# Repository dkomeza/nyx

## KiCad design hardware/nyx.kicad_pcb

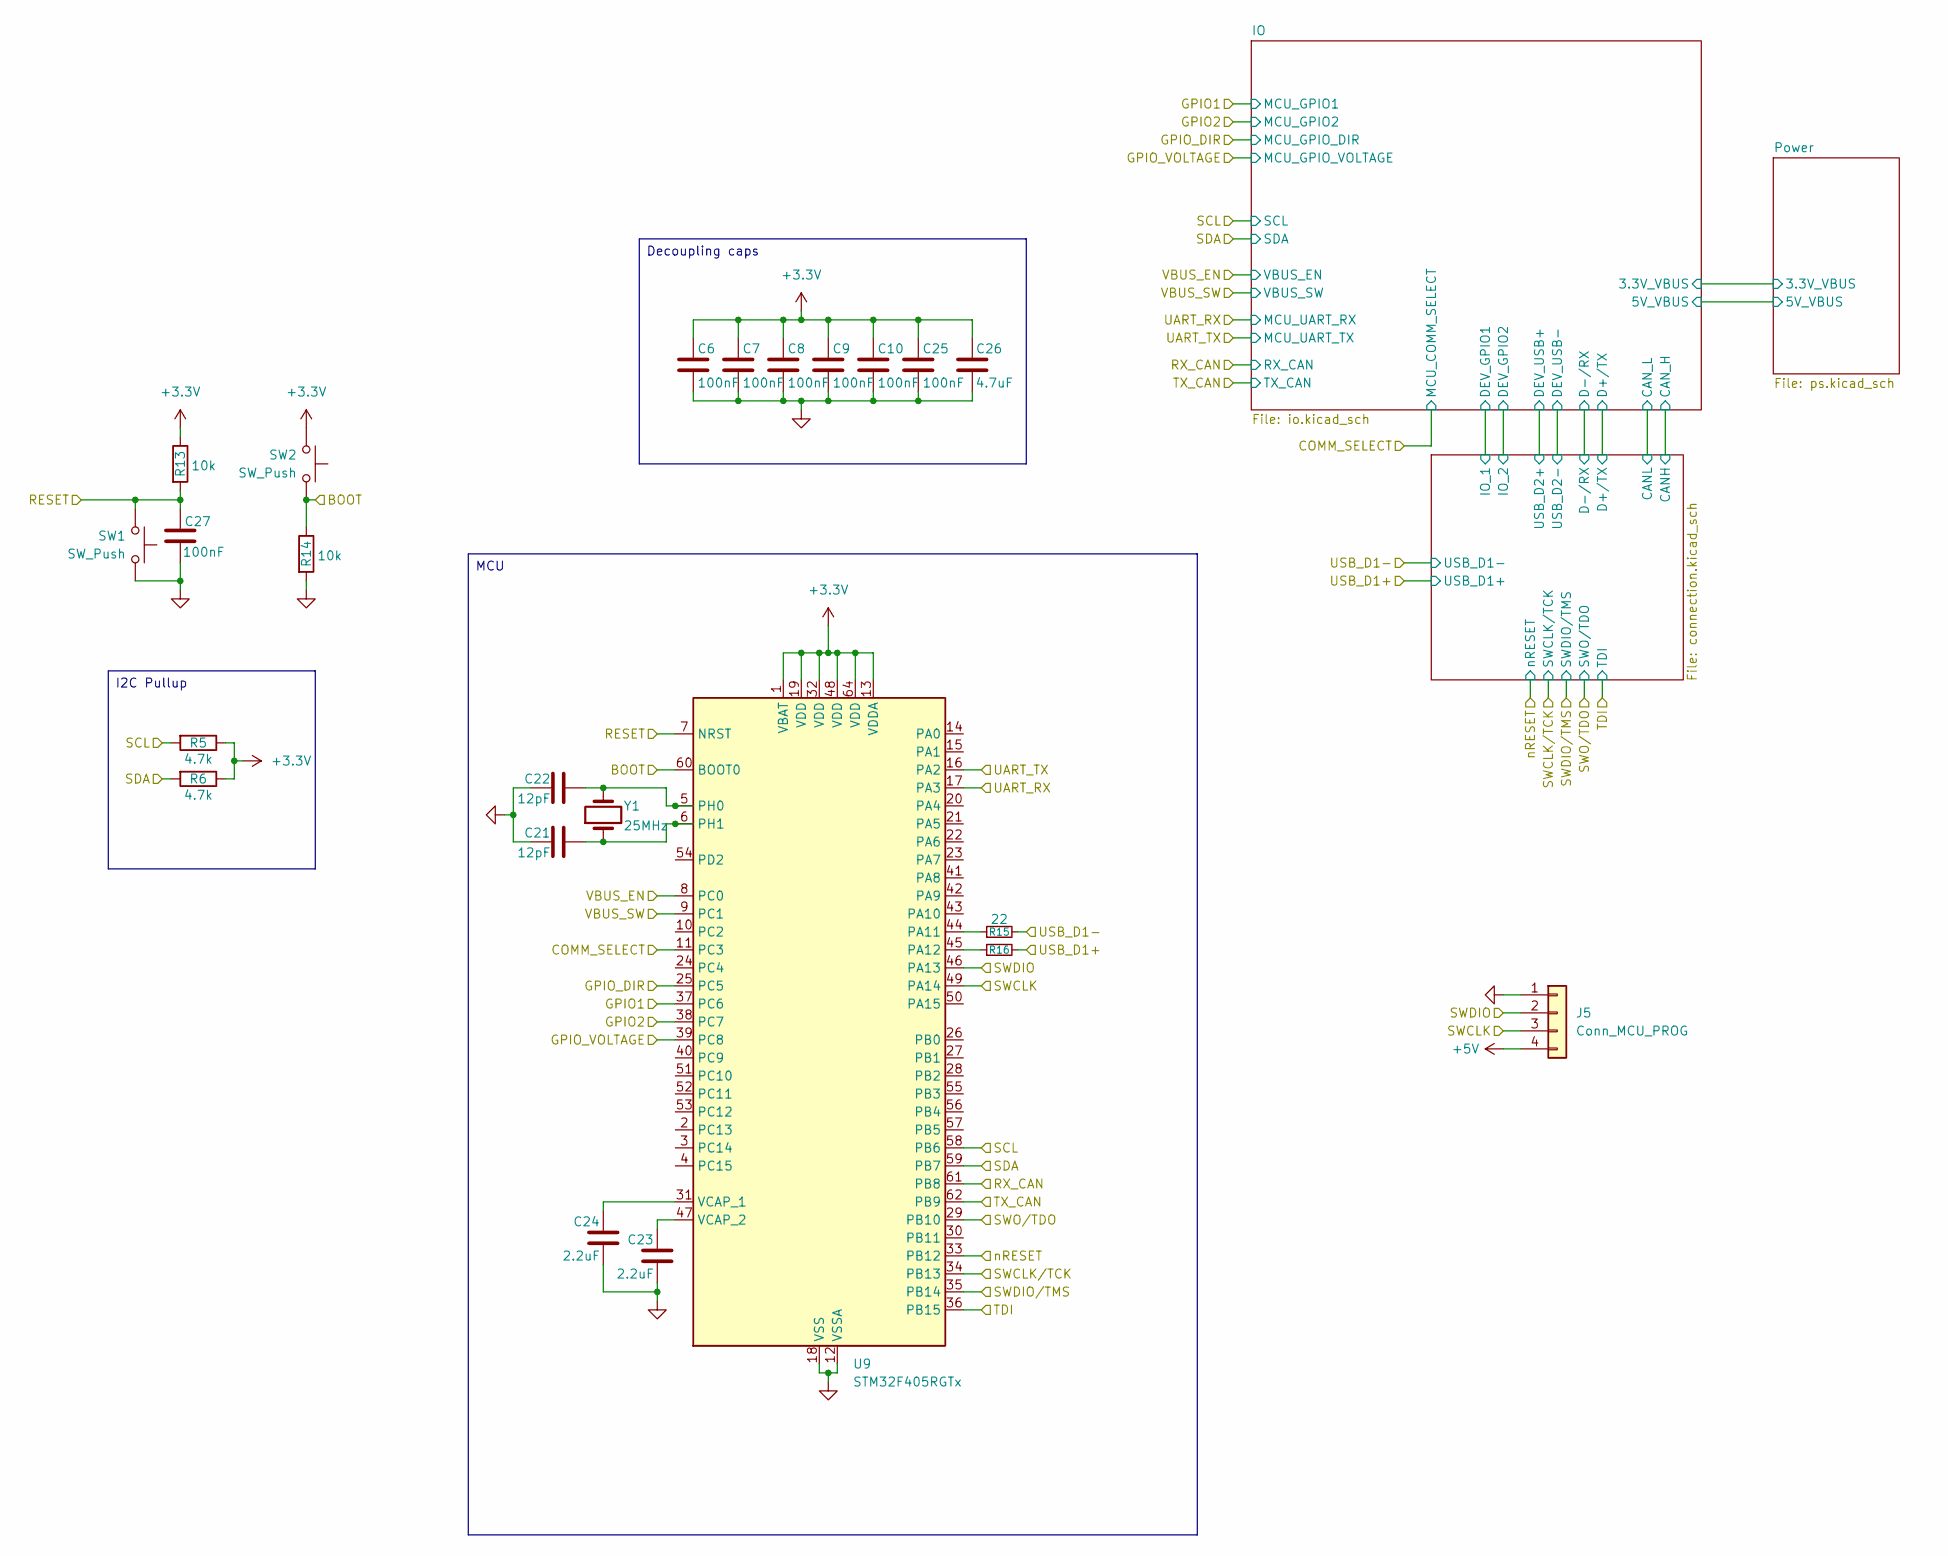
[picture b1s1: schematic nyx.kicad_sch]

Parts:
C6, C7, C8, C9, C10, C25, C27: 100nF; C_0402_1005Metric
C21, C22: 12pF; C_0402_1005Metric
C23, C24: 2.2uF; C_0603_1608Metric
C26: 4.7uF; C_0603_1608Metric
J5: Conn_MCU_PROG; PinHeader_1x04_P2.54mm_Vertical
R5, R6: 4.7k; R_0603_1608Metric
R13, R14: 10k; R_0603_1608Metric
R15, R16: 22; R_0603_1608Metric
SW1, SW2: SW_Push; SW_SPST_B3U-1000P
U9: STM32F405RGTx; LQFP-64_10x10mm_P0.5mm
Y1: 25MHz; Crystal_SMD_2016-4Pin_2.0x1.6mm

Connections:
+3.3V: C6.1, C7.1, C8.1, C9.1, C10.1, C25.1, C26.1, R5.1, R6.1, R13.1, SW2.2, U9.1 (VBAT), U9.13 (VDDA), U9.19 (VDD), U9.32 (VDD), U9.48 (VDD), U9.64 (VDD); also elsewhere on the board
+5V: J5.4; also elsewhere on the board
/BOOT: R14.1, SW2.1, U9.60 (BOOT0)
/COMM_SELECT: U9.11 (PC3); also elsewhere on the board
/GPIO1: U9.37 (PC6); also elsewhere on the board
/GPIO2: U9.38 (PC7); also elsewhere on the board
/GPIO_DIR: U9.25 (PC5); also elsewhere on the board
/GPIO_VOLTAGE: U9.39 (PC8); also elsewhere on the board
/RESET: C27.1, R13.2, SW1.2, U9.7 (NRST)
/RX_CAN: U9.61 (PB8); also elsewhere on the board
/SCL: R5.2, U9.58 (PB6); also elsewhere on the board
/SDA: R6.2, U9.59 (PB7); also elsewhere on the board
/SWCLK: J5.3, U9.49 (PA14)
/SWCLK/TCK: U9.34 (PB13); also elsewhere on the board
/SWDIO: J5.2, U9.46 (PA13)
/SWDIO/TMS: U9.35 (PB14); also elsewhere on the board
/SWO/TDO: U9.29 (PB10); also elsewhere on the board
/TDI: U9.36 (PB15); also elsewhere on the board
/TX_CAN: U9.62 (PB9); also elsewhere on the board
/UART_RX: U9.17 (PA3); also elsewhere on the board
/UART_TX: U9.16 (PA2); also elsewhere on the board
/USB_D1+: R16.2; also elsewhere on the board
/USB_D1-: R15.2; also elsewhere on the board
/VBUS_EN: U9.8 (PC0); also elsewhere on the board
/VBUS_SW: U9.9 (PC1); also elsewhere on the board
/nRESET: U9.33 (PB12); also elsewhere on the board
GND: C6.2, C7.2, C8.2, C9.2, C10.2, C21.1, C22.1, C23.2, C24.2, C25.2, C26.2, C27.2, J5.1, R14.2, SW1.1, U9.12 (VSSA), U9.18 (VSS), U9.63 (VSS); also elsewhere on the board
unnamed: R15.1, U9.44 (PA11)
unnamed: R16.1, U9.45 (PA12)
unnamed: C22.2, U9.5 (PH0), Y1.2
unnamed: C21.2, U9.6 (PH1), Y1.1
unnamed: C24.1, U9.31 (VCAP_1)
unnamed: C23.1, U9.47 (VCAP_2)

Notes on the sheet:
I2C Pullup
MCU
Decoupling caps

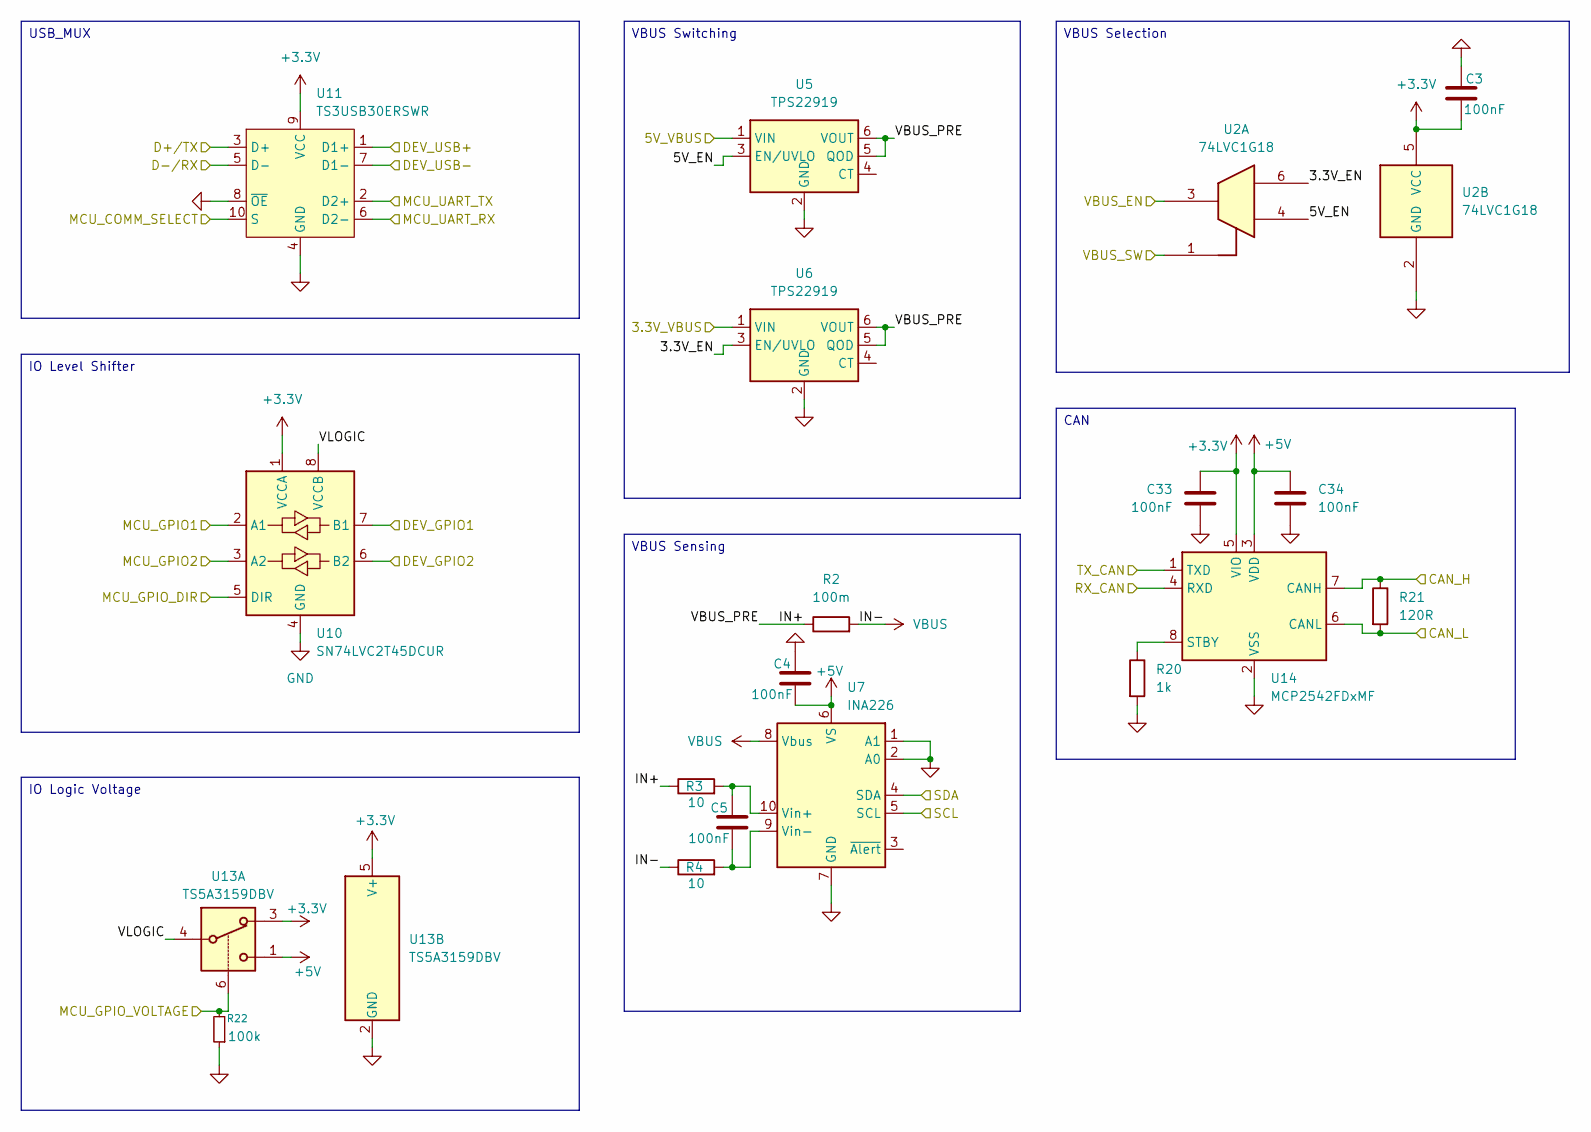
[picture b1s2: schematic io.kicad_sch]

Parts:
C3, C4, C5, C33, C34: 100nF; C_0402_1005Metric
R2: 100m; R_1206_3216Metric
R3, R4: 10; R_0603_1608Metric
R20: 1k; R_0603_1608Metric
R21: 120R; R_0603_1608Metric
R22: 100k; R_0603_1608Metric
U2: 74LVC1G18; SOT-363_SC-70-6
U5, U6: TPS22919; SOT-363_SC-70-6
U7: INA226; VSSOP-10_3x3mm_P0.5mm
U10: SN74LVC2T45DCUR; VSSOP-8_2.3x2mm_P0.5mm
U11: TS3USB30ERSWR; UQFN-10_1.4x1.8mm_P0.4mm
U13: TS5A3159DBV; SOT-23-6
U14: MCP2542FDxMF; DFN-8-1EP_3x3mm_P0.65mm_EP1.55x2.4mm

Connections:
+3.3V: C3.2, C33.1, U2.5 (VCC), U10.1 (VCCA), U11.9 (VCC), U13.3, U13.5 (V+), U14.5 (VIO); also elsewhere on the board
+5V: C4.2, C34.1, U7.6 (VS), U13.1, U14.3 (VDD); also elsewhere on the board
/COMM_SELECT: U11.10 (S); also elsewhere on the board
/Connection/CANH: R21.1, U14.7 (CANH); also elsewhere on the board
/Connection/CANL: R21.2, U14.6 (CANL); also elsewhere on the board
/Connection/D+/TX: U11.3 (D+); also elsewhere on the board
/Connection/D-/RX: U11.5 (D-); also elsewhere on the board
/Connection/IO_1: U10.7 (B1); also elsewhere on the board
/Connection/IO_2: U10.6 (B2); also elsewhere on the board
/Connection/USB_D2+: U11.1 (D1+); also elsewhere on the board
/Connection/USB_D2-: U11.7 (D1-); also elsewhere on the board
/GPIO1: U10.2 (A1); also elsewhere on the board
/GPIO2: U10.3 (A2); also elsewhere on the board
/GPIO_DIR: U10.5 (DIR); also elsewhere on the board
/GPIO_VOLTAGE: R22.2, U13.6; also elsewhere on the board
/IO/3.3V_EN: U2.6, U6.3 (EN/UVLO)
/IO/3.3V_VBUS: U6.1 (VIN); also elsewhere on the board
/IO/5V_EN: U2.4, U5.3 (EN/UVLO)
/IO/5V_VBUS: U5.1 (VIN)
/IO/IN+: R2.1, R3.1, U5.5 (QOD), U5.6 (VOUT), U6.5 (QOD), U6.6 (VOUT)
/IO/VLOGIC: U10.8 (VCCB), U13.4
/RX_CAN: U14.4 (RXD); also elsewhere on the board
/SCL: U7.5 (SCL); also elsewhere on the board
/SDA: U7.4 (SDA); also elsewhere on the board
/TX_CAN: U14.1 (TXD); also elsewhere on the board
/UART_RX: U11.6 (D2-); also elsewhere on the board
/UART_TX: U11.2 (D2+); also elsewhere on the board
/VBUS_EN: U2.3; also elsewhere on the board
/VBUS_SW: U2.1; also elsewhere on the board
GND: C3.1, C4.1, C33.2, C34.2, R20.2, R22.1, U2.2 (GND), U5.2 (GND), U6.2 (GND), U7.1 (A1), U7.2 (A0), U7.7 (GND), U10.4 (GND), U11.4 (GND), U11.8 (~OE), U13.2 (GND), U14.2 (VSS), U14.9 (VSS); also elsewhere on the board
unnamed: C5.1, R3.2, U7.10 (Vin+)
unnamed: C5.2, R4.2, U7.9 (Vin-)
unnamed: R20.1, U14.8 (STBY)
VBUS: R2.2, R4.1, U7.8 (Vbus); also elsewhere on the board

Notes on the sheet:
USB_MUX
IO Level Shifter
VBUS Selection
VBUS Sensing
IO Logic Voltage
VBUS Switching
CAN

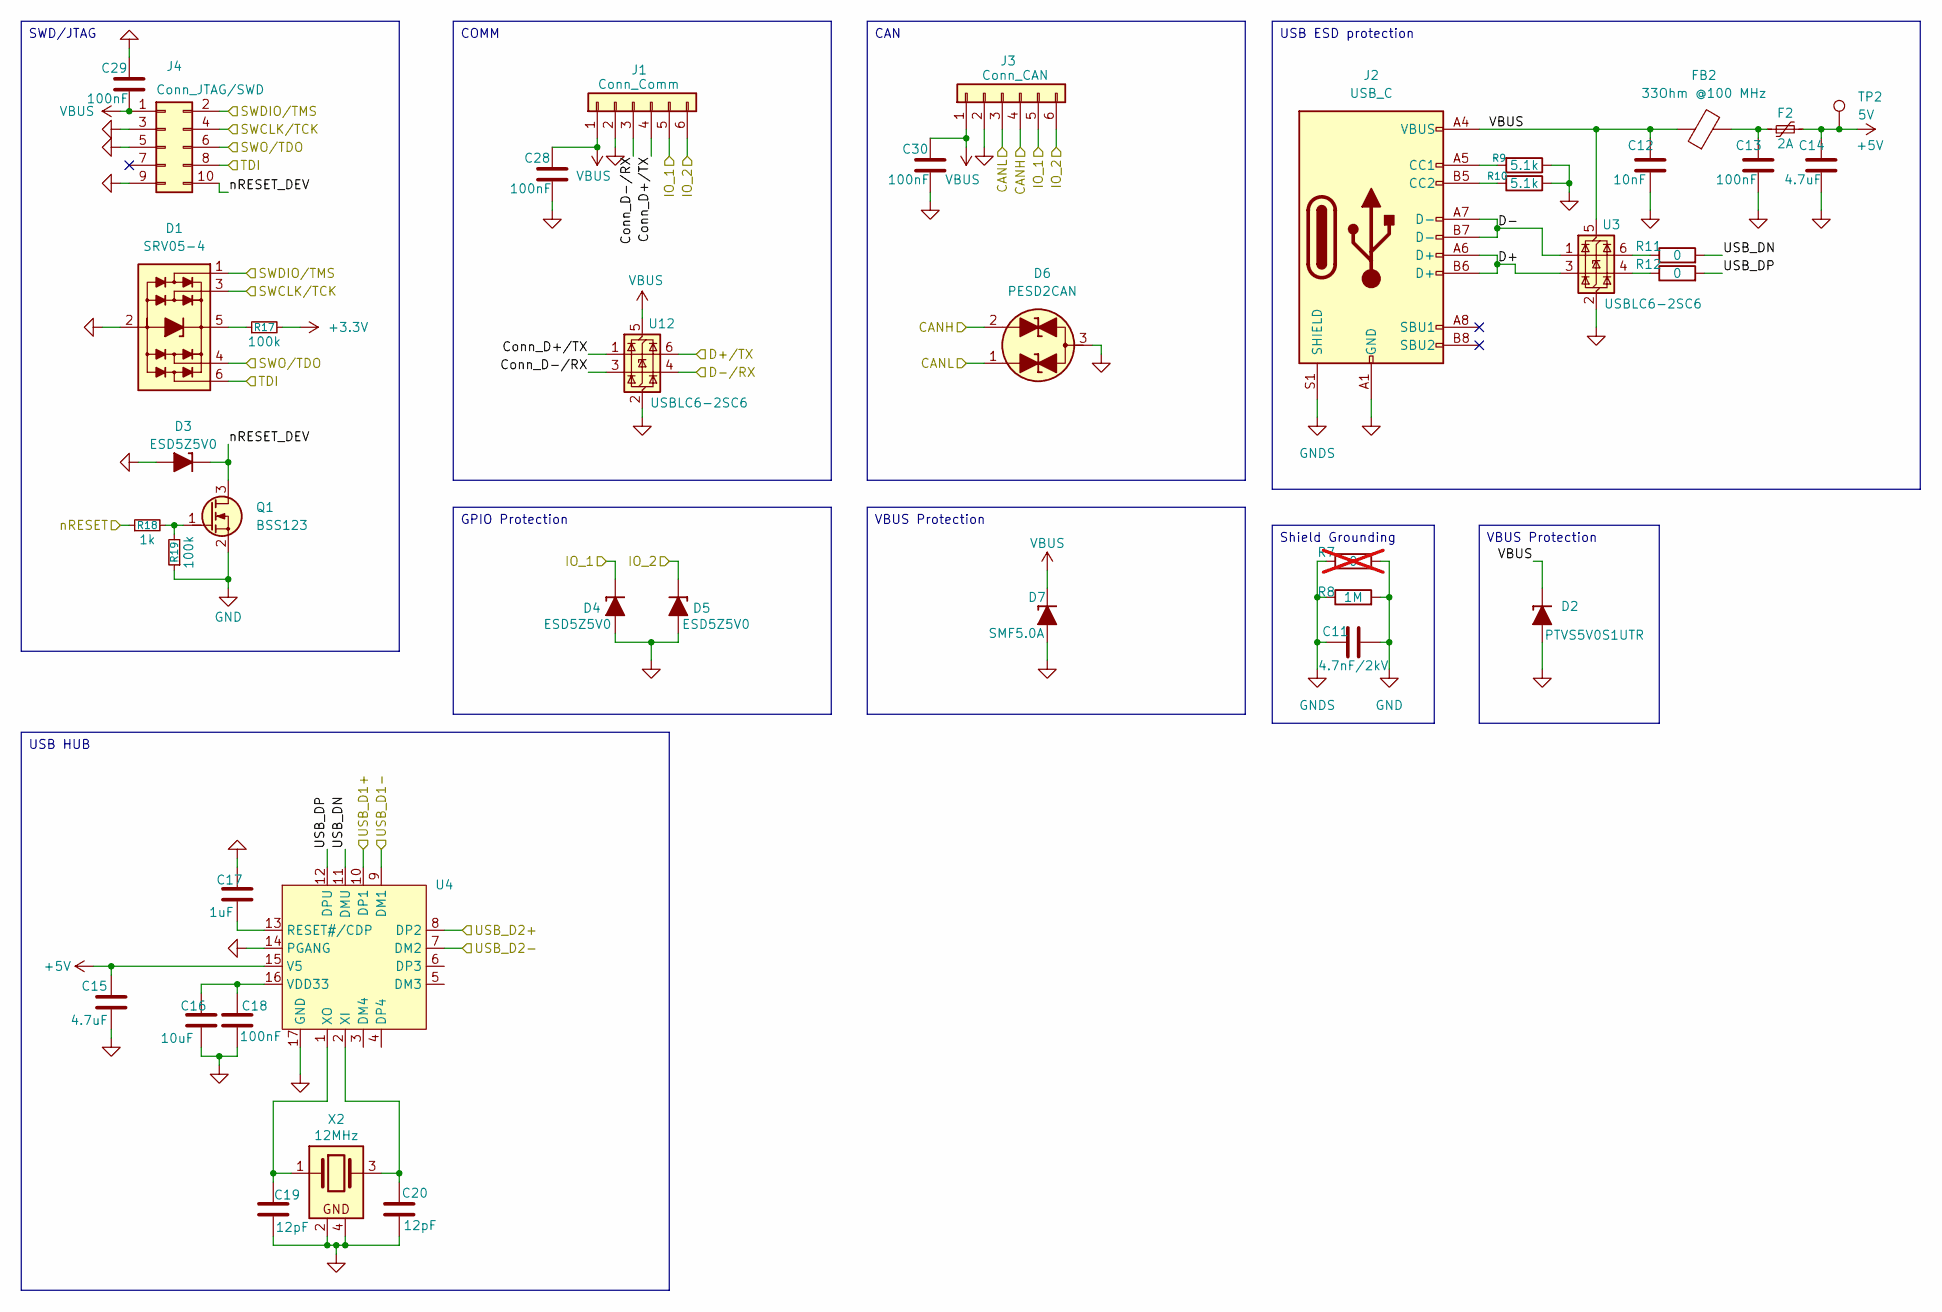
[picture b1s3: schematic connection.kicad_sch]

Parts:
C11: 4.7nF/2kV; C_1206_3216Metric
C12: 10nF; C_0603_1608Metric
C13, C18, C28, C29, C30: 100nF; C_0402_1005Metric
C14, C15: 4.7uF; C_0603_1608Metric
C16: 10uF; C_0603_1608Metric
C17: 1uF; C_0603_1608Metric
C19, C20: 12pF; C_0402_1005Metric
D1: SRV05-4; SOT-23-6
D2: PTVS5V0S1UTR; D_SOD-123
D3, D4, D5: ESD5Z5V0; D_SOD-523
D6: PESD2CAN; SOT-23
D7: SMF5.0A; D_SOD-123F
F2: 2A; Fuse_1206_3216Metric
FB2: 33Ohm @100 MHz; Ferrite_0805_2012Metric
J1: Conn_Comm; PinHeader_1x06_P2.54mm_Vertical
J2: USB_C; USB_C_Receptacle_HCTL_HC-TYPE-C-16P-01A
J3: Conn_CAN; PinHeader_1x06_P2.54mm_Vertical
J4: Conn_JTAG/SWD; PinHeader_2x05_P1.27mm_Vertical
Q1: BSS123; SOT-23
R7: 0; R_0603_1608Metric; not fitted
R8: 1M; R_0603_1608Metric
R9, R10: 5.1k; R_0603_1608Metric
R11, R12: 0; R_0603_1608Metric
R17, R19: 100k; R_0603_1608Metric
R18: 1k; R_0603_1608Metric
TP2: 5V; TestPoint_Pad_D1.0mm
U3, U12: USBLC6-2SC6; SOT-666
U4: QFN-16-1EP_3x3mm_P0.5mm_EP1.75x1.75mm
X2: 12MHz; Crystal_SMD_2016-4Pin_2.0x1.6mm

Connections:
+3.3V: R17.2; also elsewhere on the board
+5V: C14.1, C15.1, F2.2, TP2.1, U4.15 (V5); also elsewhere on the board
/Connection/CANH: D6.2 (A2), J3.4; also elsewhere on the board
/Connection/CANL: D6.1 (A1), J3.3; also elsewhere on the board
/Connection/Conn_D+/TX: J1.4, U12.1 (I/O1)
/Connection/Conn_D-/RX: J1.3, U12.3 (I/O2)
/Connection/D+: J2.A6 (D+), J2.B6 (D+), U3.3 (I/O2)
/Connection/D+/TX: U12.6 (I/O1); also elsewhere on the board
/Connection/D-: J2.A7 (D-), J2.B7 (D-), U3.1 (I/O1)
/Connection/D-/RX: U12.4 (I/O2); also elsewhere on the board
/Connection/IO_1: D4.1 (K), J1.5, J3.5; also elsewhere on the board
/Connection/IO_2: D5.1 (K), J1.6, J3.6; also elsewhere on the board
/Connection/USB_D2+: U4.8 (DP2); also elsewhere on the board
/Connection/USB_D2-: U4.7 (DM2); also elsewhere on the board
/Connection/USB_DN: R11.2, U4.11 (DMU)
/Connection/USB_DP: R12.2, U4.12 (DPU)
/Connection/nRESET_DEV: D3.1 (K), J4.10, Q1.3 (D)
/SWCLK/TCK: D1.3 (L2), J4.4; also elsewhere on the board
/SWDIO/TMS: D1.1 (L1), J4.2; also elsewhere on the board
/SWO/TDO: D1.4 (L3), J4.6; also elsewhere on the board
/TDI: D1.6 (L4), J4.8; also elsewhere on the board
/USB_D1+: U4.10 (DP1); also elsewhere on the board
/USB_D1-: U4.9 (DM1); also elsewhere on the board
/nRESET: R18.1; also elsewhere on the board
GND: C11.2, C12.2, C13.2, C14.2, C15.2, C16.2, C17.1, C18.2, C19.2, C20.2, C28.2, C29.1, C30.2, D1.2 (VN), D2.2 (A), D3.2 (A), D4.2 (A), D5.2 (A), D6.3 (Com), D7.2 (A), J1.2, J2.A1 (GND), J2.A12 (GND), J2.B1 (GND), J2.B12 (GND), J3.2, J4.3, J4.5, J4.9, Q1.2 (S), R7.2, R8.2, R9.1, R10.1, R19.1, U3.2 (GND), U4.14 (PGANG), U4.17 (GND), U12.2 (GND), X2.2, X2.4; also elsewhere on the board
GNDS: C11.1, J2.S1 (SHIELD), R7.1, R8.1
unnamed: C13.1, F2.1, FB2.2
unnamed: D1.5 (VP), R17.1
unnamed: J2.A5 (CC1), R9.2
unnamed: J2.B5 (CC2), R10.2
unnamed: Q1.1 (G), R18.2, R19.2
unnamed: R11.1, U3.6 (I/O1)
unnamed: R12.1, U3.4 (I/O2)
unnamed: C17.2, U4.13 (RESET#/CDP)
unnamed: C16.1, C18.1, U4.16 (VDD33)
unnamed: C20.1, U4.2 (XI), X2.3
unnamed: C19.1, U4.1 (XO), X2.1
VBUS: C12.1, C28.1, C29.2, C30.1, D2.1 (K), D7.1 (K), FB2.1, J1.1, J2.A4 (VBUS), J2.A9 (VBUS), J2.B4 (VBUS), J2.B9 (VBUS), J3.1, J4.1, U3.5 (VBUS), U12.5 (VBUS); also elsewhere on the board

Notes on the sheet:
COMM
USB HUB
Shield Grounding
VBUS Protection
SWD/JTAG
CAN
GPIO Protection
USB ESD protection

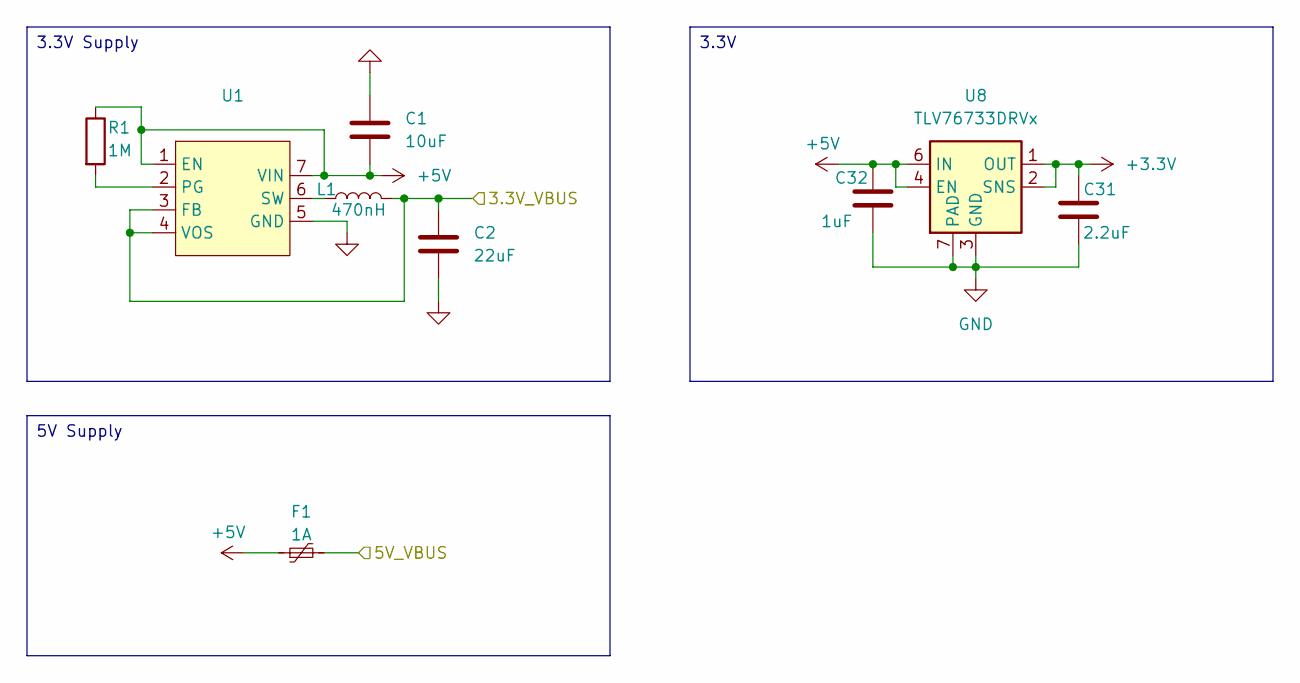
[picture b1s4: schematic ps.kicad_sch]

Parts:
C1: 10uF; C_0603_1608Metric
C2: 22uF; C_0603_1608Metric
C31: 2.2uF; C_0603_1608Metric
C32: 1uF; C_0603_1608Metric
F1: 1A; Fuse_1206_3216Metric
L1: 470nH; L_0603_1608Metric
R1: 1M; R_0603_1608Metric
U1: RLT0007A
U8: TLV76733DRVx; WSON-6-1EP_2x2mm_P0.65mm_EP1x1.6mm

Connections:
+3.3V: C31.1, U8.1 (OUT), U8.2 (SNS); also elsewhere on the board
+5V: C1.2, C32.1, F1.1, R1.1, U1.1 (EN), U1.7 (VIN), U8.4 (EN), U8.6 (IN); also elsewhere on the board
/IO/3.3V_VBUS: C2.1, L1.2, U1.3 (FB), U1.4 (VOS); also elsewhere on the board
GND: C1.1, C2.2, C31.2, C32.2, U1.5 (GND), U8.3 (GND), U8.5 (GND), U8.7 (PAD); also elsewhere on the board
unnamed: L1.1, U1.6 (SW)
unnamed: R1.2, U1.2 (PG)

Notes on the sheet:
3.3V Supply
3.3V
5V Supply

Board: 2 copper layers, 84 parts (0 on the bottom side), 66 nets, no tracks yet.

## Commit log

2025-07-15 ✨ Power management section updates
2025-12-11 🔨 Move files to a new directory
2025-12-11 ✨ Complete footprint assignment
